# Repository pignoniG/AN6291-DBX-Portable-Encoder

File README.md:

AN6291 based DBX Portable Encoder with premplifier for electrect micropones.
Beware, for reliability (aka avoid switches), this can only perform as an encoder.

BOM -> https://pignonig.github.io/AN6291-DBX-Portable-Encoder/AN6291_encoder/bom/ibom.html

Online kikad visualization -> https://kicanvas.org/?repo=https%3A%2F%2Fgithub.com%2FpignoniG%2FAN6291-DBX-Portable-Encoder%2Ftree%2Fmain%2FAN6291_encoder

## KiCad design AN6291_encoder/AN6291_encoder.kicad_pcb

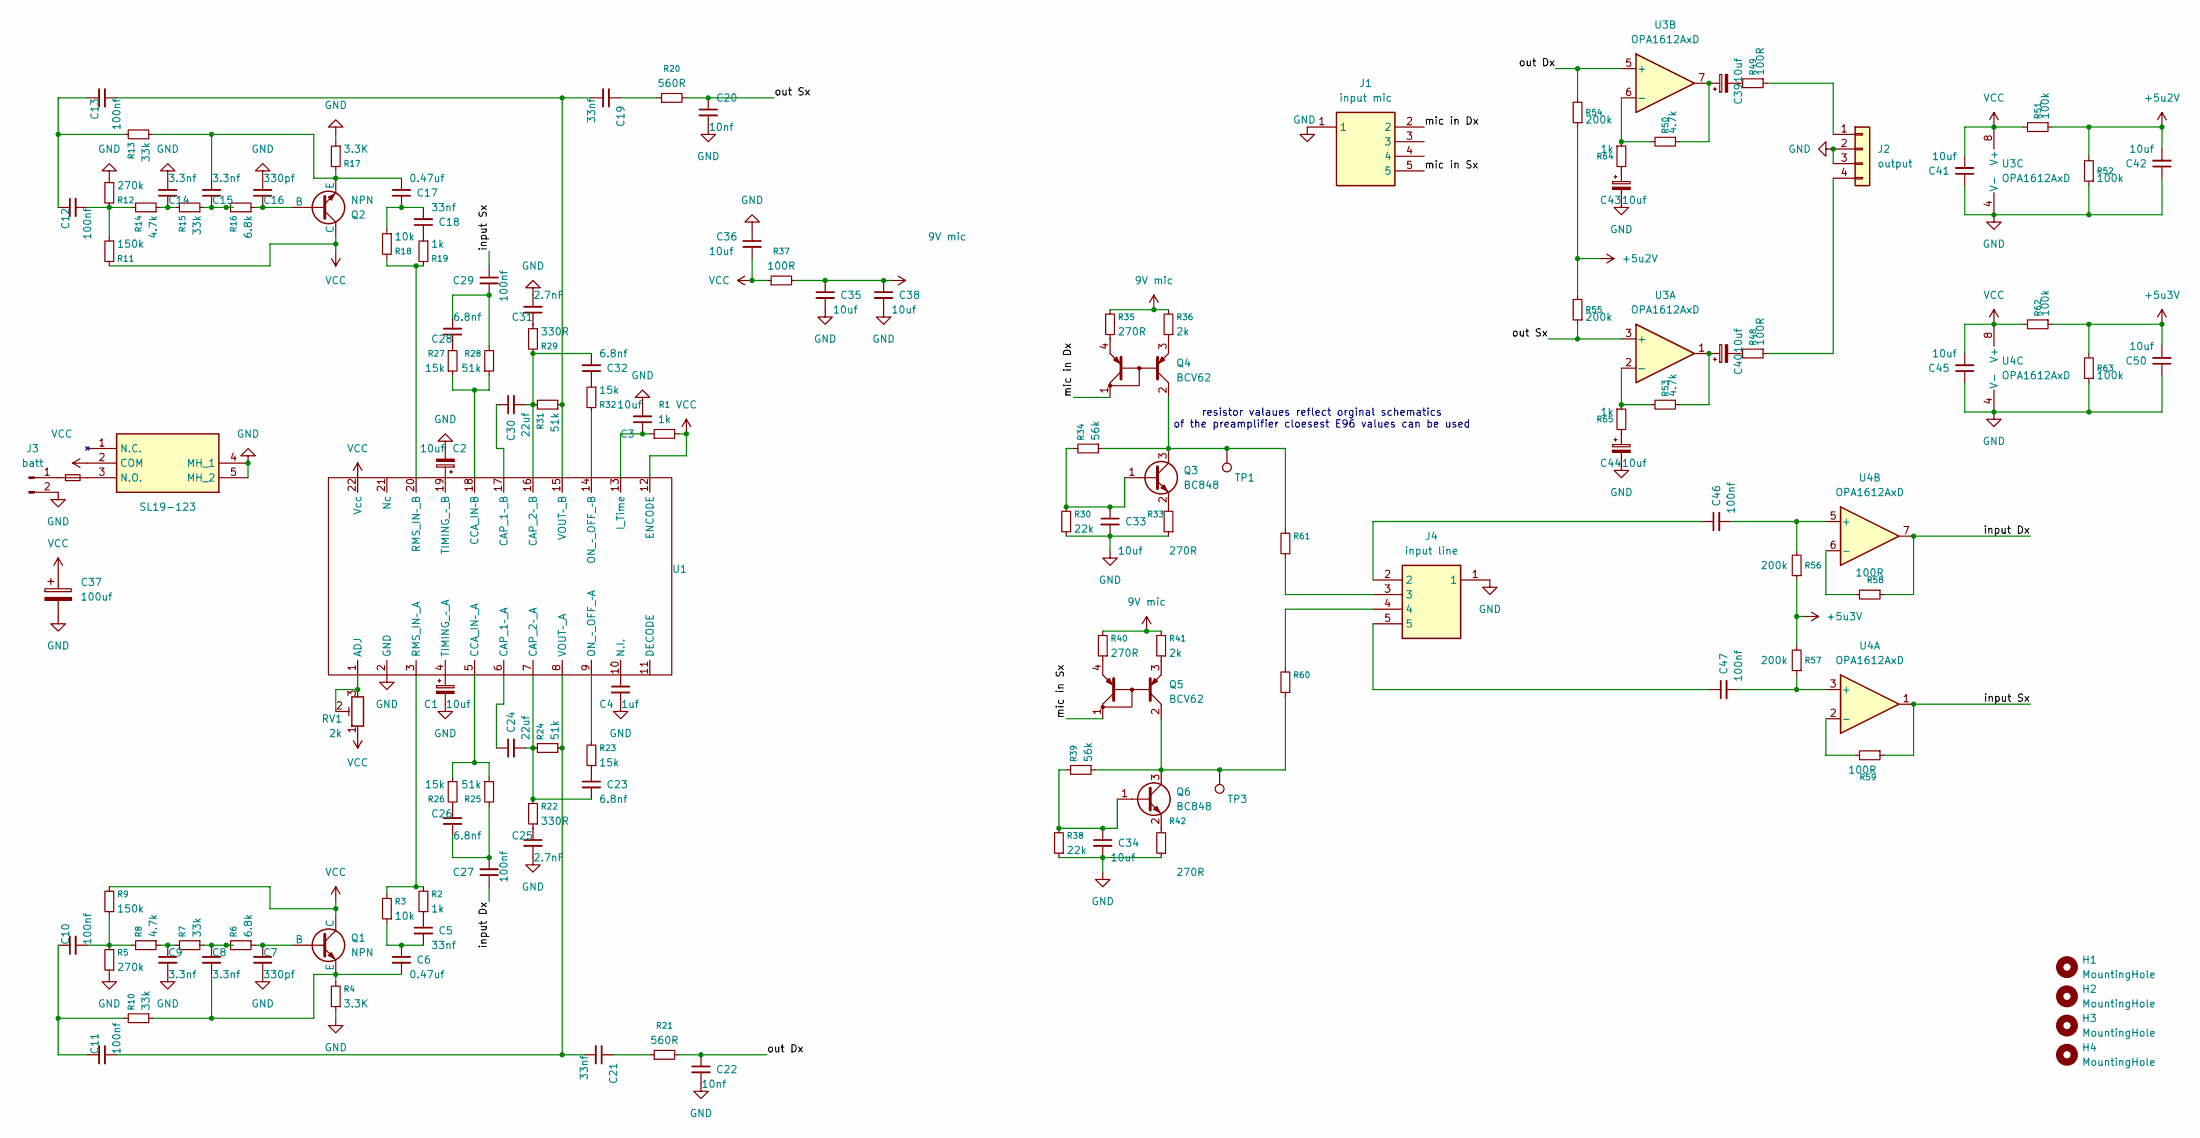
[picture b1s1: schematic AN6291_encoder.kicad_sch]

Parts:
C1, C2, C39, C40, C43, C44: 10uf; C_1206_3216Metric
C3, C33, C34, C35, C36, C38, C41, C42, C45, C50: 10uf; C_0805_2012Metric
C4: 1uf; C_0805_2012Metric
C5, C18, C19, C21: 33nf; C_0805_2012Metric
C6, C17: 0.47uf; C_1206_3216Metric
C7, C16: 330pf; C_0805_2012Metric
C8, C9, C14, C15: 3.3nf; C_0805_2012Metric
C10, C11, C12, C13, C27, C29, C46, C47: 100nf; C_1206_3216Metric
C20, C22: 10nf; C_0805_2012Metric
C23, C26, C28, C32: 6.8nf; C_0805_2012Metric
C24, C30: 22uf; C_1206_3216Metric
C25, C31: 2.7nF; C_0805_2012Metric
C37: 100uf; CP_Radial_D10.0mm_P5.00mm
F1: Fuse_Small; Fuse_1206_3216Metric_Pad1.42x1.75mm_HandSolder
H1, H2, H3, H4: MountingHole; MountingHole_3.2mm_M3_DIN965_Pad_TopBottom
J1: input mic; JY0395PFC68133; Manufacturer_Part_Number JY039-5P (FC68133)
J2: output; Molex_KK-254_AE-6410-04A_1x04_P2.54mm_Vertical
J3: batt; PinHeader_1x02_P2.54mm_Vertical
J4: input line; JY0395PFC68133; Manufacturer_Part_Number JY039-5P (FC68133)
Q1, Q2: NPN; TO-92
Q3, Q6: BC848; SOT-23
Q4, Q5: BCV62; SOT-143
R1, R2, R19, R64, R65: 1k; R_0805_2012Metric; JLCPCB Part C17513
R3, R18: 10k; R_0805_2012Metric; JLCPCB Part C17414
R4, R17: 3.3K; R_0805_2012Metric; JLCPCB Part C26010
R5, R12: 270k; R_0805_2012Metric; JLCPCB Part C17589
R6, R16: 6.8k; R_0805_2012Metric; JLCPCB Part C17772
R7, R10, R13, R15: 33k; R_0805_2012Metric; JLCPCB Part C17633
R8, R14, R50, R53: 4.7k; R_0805_2012Metric; JLCPCB Part C17673
R9, R11: 150k; R_0805_2012Metric; JLCPCB Part C17470
R20, R21: 560R; R_0805_2012Metric; JLCPCB Part C28636
R22, R29: 330R; R_0805_2012Metric; JLCPCB Part C17630
R23, R26, R27, R32: 15k; R_0805_2012Metric; JLCPCB Part C17475
R24, R25, R28, R31: 51k; R_0805_2012Metric; JLCPCB Part C17737
R30, R38: 22k; R_0805_2012Metric; JLCPCB Part C17560
R33, R35, R40, R42: 270R; R_0805_2012Metric; JLCPCB Part C17590
R34, R39: 56k; R_0805_2012Metric; JLCPCB Part C17756
R36, R41: 2k; R_0805_2012Metric; JLCPCB Part C17604
R37, R48, R49, R58, R59, R60, R61: 100R; R_0805_2012Metric; JLCPCB Part C17408
R51, R52, R62, R63: 100k; R_0805_2012Metric; JLCPCB Part C149504
R54, R55, R56, R57: 200k; R_0805_2012Metric; JLCPCB Part C17539
RV1: 2k; Potentiometer_Vishay_TS53YL_Vertical
S1: SL19-123; SL19123; Manufacturer_Part_Number SL19-123
TP1, TP3: TestPoint; PinHeader_1x01_P1.00mm_Vertical
U1: DIP-22_W10.16mm_LongPads
U3, U4: OPA1612AxD; SOIC-8_3.9x4.9mm_P1.27mm

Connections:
9V mic: C35.1, C38.1, R35.2, R36.2, R37.2, R40.2, R41.2
+5u2V: C42.2, R51.1, R52.2, R54.1, R55.2
+5u3V: C50.2, R56.1, R57.2, R62.1, R63.2
/input Dx: C27.1, R58.1, U4.7
/input Sx: C29.1, R59.1, U4.1
/mic in Dx: J1.2, Q4.1 (C2)
/mic in Sx: J1.5, Q5.1 (C2)
/out Dx: C22.1, R21.2, R54.2, U3.5 (+)
/out Sx: C20.1, R20.2, R55.1, U3.3 (+)
GND: C1.2, C2.2, C3.2, C4.2, C7.2, C9.2, C14.2, C16.2, C20.2, C22.2, C25.2, C31.2, C33.2, C34.2, C35.2, C36.1, C37.2, C38.2, C41.1, C42.1, C43.2, C44.2, C45.1, C50.1, J1.1, J2.2, J2.3, J3.2, J4.1, R4.1, R5.1, R12.1, R17.1, R30.1, R33.1, R38.1, R42.1, R52.1, R63.1, S1.4 (MH_1), S1.5 (MH_2), U1.2 (GND), U3.4 (V-), U4.4 (V-)
unnamed: C5.1, R2.1
unnamed: C5.2, C6.1, R3.1
unnamed: C8.1, R6.2, R7.1
unnamed: C9.1, R7.2, R8.1
unnamed: C10.1, C11.1, R10.2
unnamed: C10.2, R5.2, R8.2, R9.1
unnamed: C12.1, C13.1, R13.2
unnamed: C12.2, R11.1, R12.2, R14.2
unnamed: C14.1, R14.1, R15.2
unnamed: C15.1, R15.1, R16.2
unnamed: C17.1, C18.2, R18.1
unnamed: C18.1, R19.1
unnamed: C19.1, R20.1
unnamed: C21.1, R21.1
unnamed: C23.1, R23.1
unnamed: C25.1, R22.1
unnamed: C26.1, R26.2
unnamed: C26.2, C27.2, R25.2
unnamed: C28.1, R27.2
unnamed: C28.2, C29.2, R28.2
unnamed: C31.1, R29.1
unnamed: C32.1, R32.1
unnamed: C39.1, R50.1, U3.7
unnamed: C39.2, R49.2
unnamed: C40.1, R53.1, U3.1
unnamed: C40.2, R48.2
unnamed: C43.1, R64.2
unnamed: C44.1, R65.2
unnamed: C46.1, J4.2
unnamed: C47.1, J4.5
unnamed: J2.1, R49.1
unnamed: J2.4, R48.1
unnamed: F1.1, J3.1
unnamed: J4.3, R61.1
unnamed: J4.4, R60.2
unnamed: C7.1, Q1.3 (B), R6.1
unnamed: C6.2, C8.2, Q1.1 (E), R4.2, R10.1
unnamed: C16.1, Q2.3 (B), R16.1
unnamed: C15.2, C17.2, Q2.1 (E), R13.1, R17.2
unnamed: C33.1, Q3.1 (B), R30.2, R34.2
unnamed: Q3.3 (C), Q4.2 (C1), R34.1, R61.2, TP1.1
unnamed: Q3.2 (E), R33.2
unnamed: Q4.3 (E1), R36.1
unnamed: Q4.4 (E2), R35.1
unnamed: Q5.2 (C1), Q6.3 (C), R39.1, R60.1, TP3.1
unnamed: Q5.3 (E1), R41.1
unnamed: Q5.4 (E2), R40.1
unnamed: C34.1, Q6.1 (B), R38.2, R39.2
unnamed: Q6.2 (E), R42.2
unnamed: F1.2, S1.3 (N.O.)
unnamed: RV1.2, RV1.3, U1.1 (ADJ)
unnamed: C24.1, U1.6 (CAP_1–_A)
unnamed: C30.1, U1.17 (CAP_1–_B)
unnamed: C23.2, C24.2, R22.2, R24.2, U1.7 (CAP_2–_A)
unnamed: C30.2, C32.2, R29.2, R31.2, U1.16 (CAP_2–_B)
unnamed: R27.1, R28.1, U1.18 (CCA_IN–B)
unnamed: R25.1, R26.1, U1.5 (CCA_IN–_A)
unnamed: C3.1, R1.1, U1.13 (I_Time)
unnamed: C4.1, U1.10 (N.I.)
unnamed: R23.2, U1.9 (ON_–_OFF_–A)
unnamed: R32.2, U1.14 (ON_–_OFF_–B)
unnamed: R2.2, R3.2, U1.3 (RMS_IN–_A)
unnamed: R18.2, R19.2, U1.20 (RMS_IN–_B)
unnamed: C1.1, U1.4 (TIMING_–_A)
unnamed: C2.1, U1.19 (TIMING_–_B)
unnamed: C11.2, C21.2, R24.1, U1.8 (VOUT–_A)
unnamed: C13.2, C19.2, R31.1, U1.15 (VOUT–_B)
unnamed: R53.2, R65.1, U3.2 (-)
unnamed: R50.2, R64.1, U3.6 (-)
unnamed: C47.2, R57.1, U4.3 (+)
unnamed: R59.2, U4.2 (-)
unnamed: C46.2, R56.2, U4.5 (+)
unnamed: R58.2, U4.6 (-)
VCC: C36.2, C37.1, C41.2, C45.2, Q1.2 (C), Q2.2 (C), R1.2, R9.2, R11.2, R37.1, R51.2, R62.2, RV1.1, S1.2 (COM), U1.12 (ENCODE), U1.22 (Vcc), U3.8 (V+), U4.8 (V+)

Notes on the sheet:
resistor valaues reflect orginal schematics of the preamplifier cloesest E96 values can be used

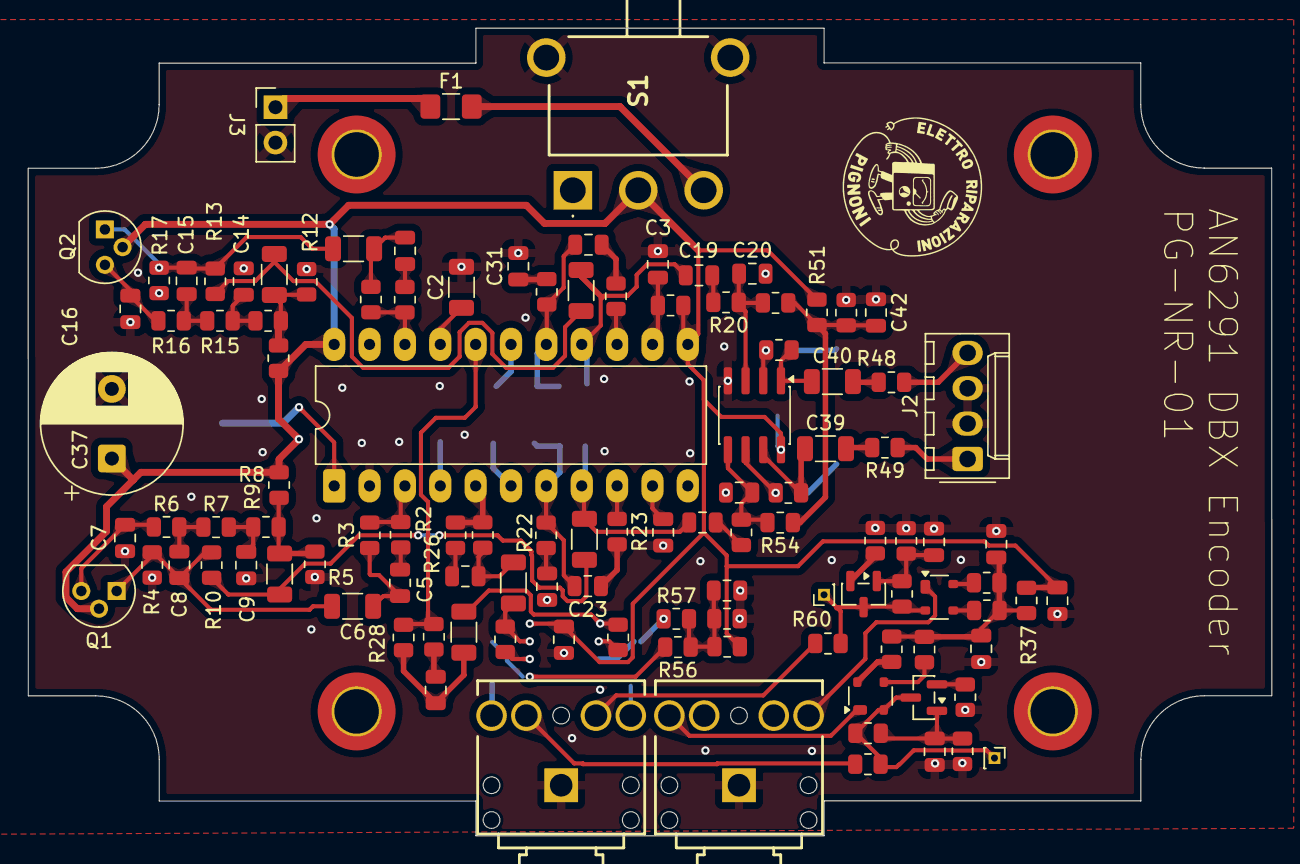
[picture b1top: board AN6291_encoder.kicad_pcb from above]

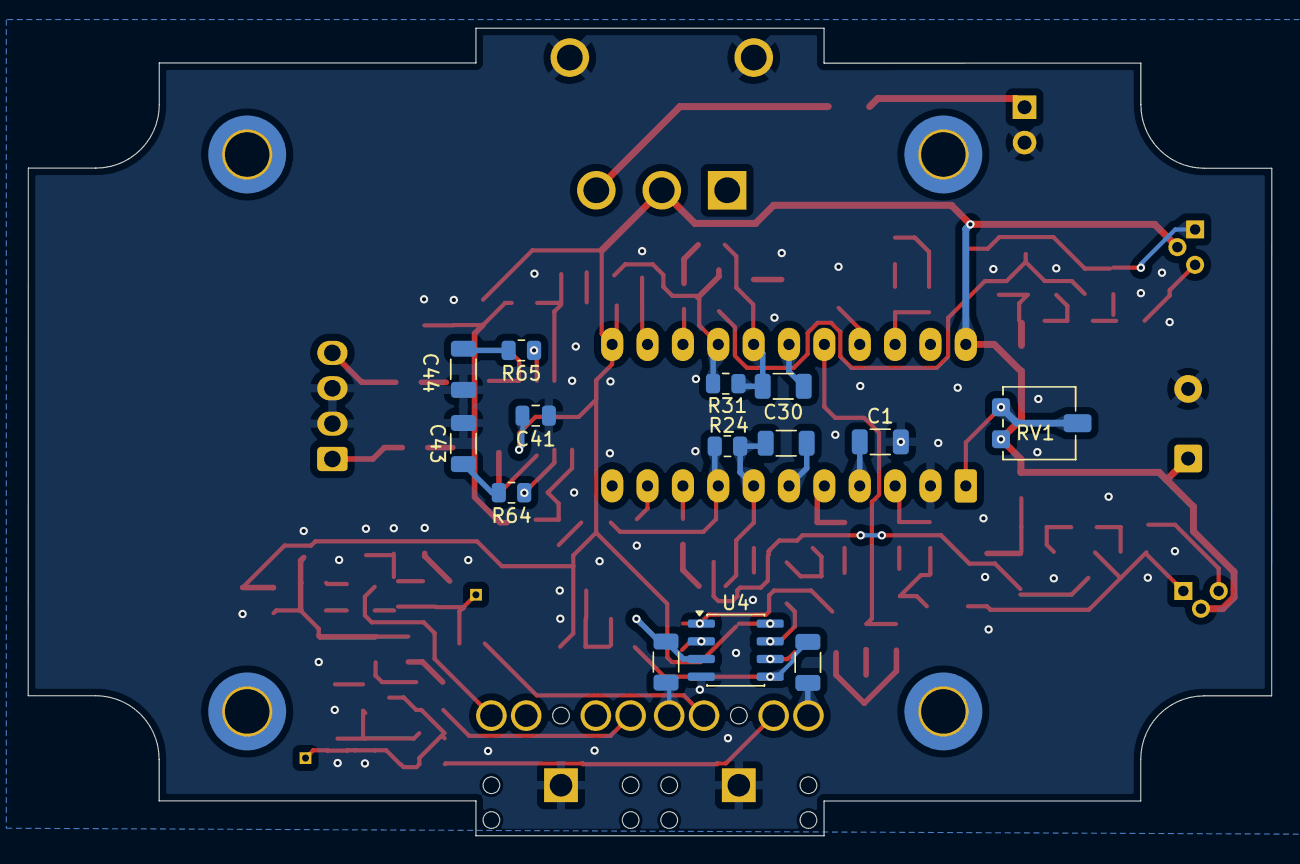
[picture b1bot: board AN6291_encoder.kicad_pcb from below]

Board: 2 copper layers, 89.3 x 58.0 mm, 130 parts (14 on the bottom side), 84 nets.

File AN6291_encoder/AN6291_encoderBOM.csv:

"Reference","Qty","Value","JLCPCB Part","Footprint","Datasheet"
"C7,C16","2","330pf","","Capacitor_SMD:C_0805_2012Metric","~"
"C25,C31","2","2.7nF","","Capacitor_SMD:C_0805_2012Metric","~"
"C8,C9,C14,C15","4","3.3nf","","Capacitor_SMD:C_0805_2012Metric","~"
"C23,C26,C28,C32","4","6.8nf","","Capacitor_SMD:C_0805_2012Metric","~"
"C20,C22","2","10nf","","Capacitor_SMD:C_0805_2012Metric","~"
"C5,C18,C19,C21","4","33nf","","Capacitor_SMD:C_0805_2012Metric","~"
"C27,C29","2","0.1uf","","Capacitor_SMD:C_1206_3216Metric","~"
"C46,C47","2","100nf","","Capacitor_SMD:C_1206_3216Metric","~"
"C10,C11,C12,C13","4","100n","","Capacitor_SMD:C_1206_3216Metric","~"
"C6,C17","2","0.47uf","","Capacitor_SMD:C_1206_3216Metric","~"
"C4","1","1uf","","Capacitor_SMD:C_0805_2012Metric","~"
"C1,C2,C39,C40,C43,C44","6","10uf","","Capacitor_SMD:C_1206_3216Metric","~"
"C3,C33,C34,C35,C36,C38,C41,C42,C45,C50","10","10uf","","Capacitor_SMD:C_0805_2012Metric","~"
"C24,C30","2","22uf","","Capacitor_SMD:C_1206_3216Metric","~"
"C37","1","100uf","","Capacitor_THT:CP_Radial_D10.0mm_P5.00mm","~"
"R37,R48,R49,R58,R59,R60,R61","7","100R","C17408","Resistor_SMD:R_0805_2012Metric","~"
"R33,R35,R40,R42","4","270R","C17590","Resistor_SMD:R_0805_2012Metric","~"
"R22,R29","2","330R","C17630","Resistor_SMD:R_0805_2012Metric","~"
"R20,R21","2","560R","C28636","Resistor_SMD:R_0805_2012Metric","~"
"R1,R2,R19","3","1k","C17513","Resistor_SMD:R_0805_2012Metric","~"
"R64,R65","2","1k","C17513","Resistor_SMD:R_0805_2012Metric","~"
"R36,R41","2","2k","C17604","Resistor_SMD:R_0805_2012Metric","~"
"RV1","1","2k","","Potentiometer_SMD:Potentiometer_Vishay_TS53YL_Vertical","~"
"R4,R17","2","3.3K","C26010","Resistor_SMD:R_0805_2012Metric","~"
"R8,R14,R50,R53","4","4.7k","C17673","Resistor_SMD:R_0805_2012Metric","~"
"R6,R16","2","6.8k","C17772","Resistor_SMD:R_0805_2012Metric","~"
"R3,R18","2","10k","C17414","Resistor_SMD:R_0805_2012Metric","~"
"R23,R26,R27,R32","4","15k","C17475","Resistor_SMD:R_0805_2012Metric","~"
"R30,R38","2","22k","C17560","Resistor_SMD:R_0805_2012Metric","~"
"R7,R10,R13,R15","4","33k","C17633","Resistor_SMD:R_0805_2012Metric","~"
"R24,R31","2","51k","C17737","Resistor_SMD:R_0805_2012Metric","~"
"R25,R28","2","51k","C17737","Resistor_SMD:R_0805_2012Metric","~"
"R34,R39","2","56k","C17756","Resistor_SMD:R_0805_2012Metric","~"
"R51,R52,R62,R63","4","100k","C149504","Resistor_SMD:R_0805_2012Metric","~"
"R9,R11","2","150k","C17470","Resistor_SMD:R_0805_2012Metric","~"
"R54,R55,R56,R57","4","200k","C17539","Resistor_SMD:R_0805_2012Metric","~"
"R5,R12","2","270k","C17589","Resistor_SMD:R_0805_2012Metric","~"
"J3","1","batt","","Connector_PinHeader_2.54mm:PinHeader_1x02_P2.54mm_Vertical","~"
"Q3,Q6","2","BC848","","Package_TO_SOT_SMD:SOT-23","http://www.infineon.com/dgdl/Infineon-BC847SERIES_BC848SERIE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"
"Q4,Q5","2","BCV62","","Package_TO_SOT_SMD:SOT-143","https://assets.nexperia.com/documents/data-sheet/BCV62.pdf"
"F1","1","Fuse_Small","","Fuse:Fuse_1206_3216Metric_Pad1.42x1.75mm_HandSolder","~"
"J4","1","input line","","LIB_JY039-5P__FC68133_:JY0395PFC68133","https://www.cliffuk.co.uk/products/jacksockets/fc68131.pdf"
"J1","1","input mic","","LIB_JY039-5P__FC68133_:JY0395PFC68133","https://www.cliffuk.co.uk/products/jacksockets/fc68131.pdf"
"H1,H2,H3,H4","4","MountingHole","","MountingHole:MountingHole_3.2mm_M3_DIN965_Pad_TopBottom","~"
"Q1,Q2","2","NPN","","Package_TO_SOT_THT:TO-92","KSC1845"
"U3,U4","2","OPA1612AxD","","Package_SO:SOIC-8_3.9x4.9mm_P1.27mm","http://www.ti.com/lit/ds/symlink/opa1612.pdf"
"J2","1","output","","Connector_Molex:Molex_KK-254_AE-6410-04A_1x04_P2.54mm_Vertical","~"
"S1","1","SL19-123","","SL19-123:SL19123","https://www.tme.eu/Document/8790ddf534d60e194ea4328cb05e27d2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"
"TP1,TP3","2","TestPoint","","Connector_PinHeader_1.00mm:PinHeader_1x01_P1.00mm_Vertical","~"
"U1","1","~","","Package_DIP:DIP-22_W10.16mm_LongPads",""

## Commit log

2026-03-16 Add description for AN6291 based DBX Portable Encoder
2026-03-17 Update README with additional information and links
2026-03-22 Removed voltage regulator for microphone supply now powered from 9v battery for lower noise
2026-03-28 rev B
